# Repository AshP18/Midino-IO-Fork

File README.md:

# MIDIno IO

MIDIno is an open source project to make the best Midi controller. For now it works under the ATMEGA2560 processor architecture, in this case an Arduino Mega development board was used. In future versions it is expected to respond to other embedded architectures

## MIDIno functions

 - MIDIno has 16 programmable knobs (encoders), each one will have the possibility of being mapped in any DAW (Digital Audio Workstation). If you want to control an delay, some reverb or any parameter of a digital instrument you can do it. 

- Midino also works as a Beat Machine, add instruments and play them with your MIDIno, press the knobs and create music.

## Important READMEs
 - [Arduino OneButton Library](https://github.com/Rguarnizo/Midino-IO/blob/master/lib/OneButton/README.md)
   - Includes information regarding the usage/purpose of the OneButton library.
 - [Arduino MIDI Library](https://github.com/Rguarnizo/Midino-IO/blob/master/lib/MIDI_Library/README.md)
   - Includes information regarding the usage/purpose of the MIDI_Library library.
 - [Protothreads Library](https://github.com/Rguarnizo/Midino-IO/blob/master/lib/Protothreads/README.md)
   - Includes information regarding the usage/purpose of the Protothreads library.

If you want to contribute with the project, read the CONTRIBUTING.md file.

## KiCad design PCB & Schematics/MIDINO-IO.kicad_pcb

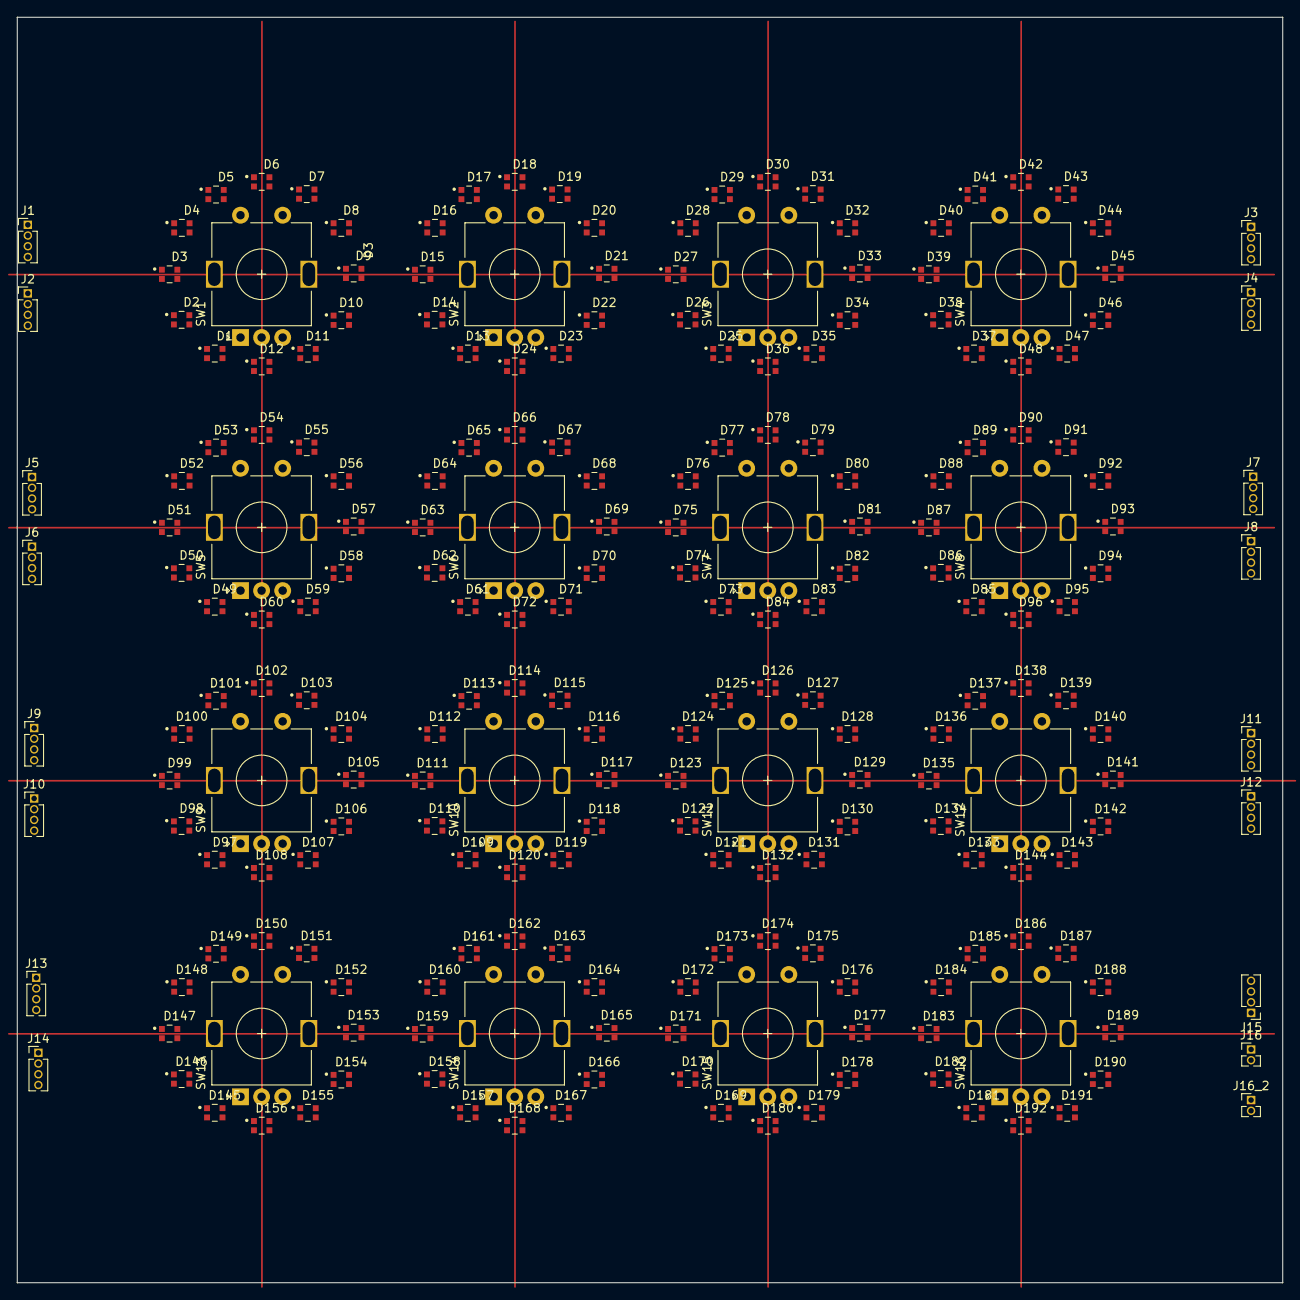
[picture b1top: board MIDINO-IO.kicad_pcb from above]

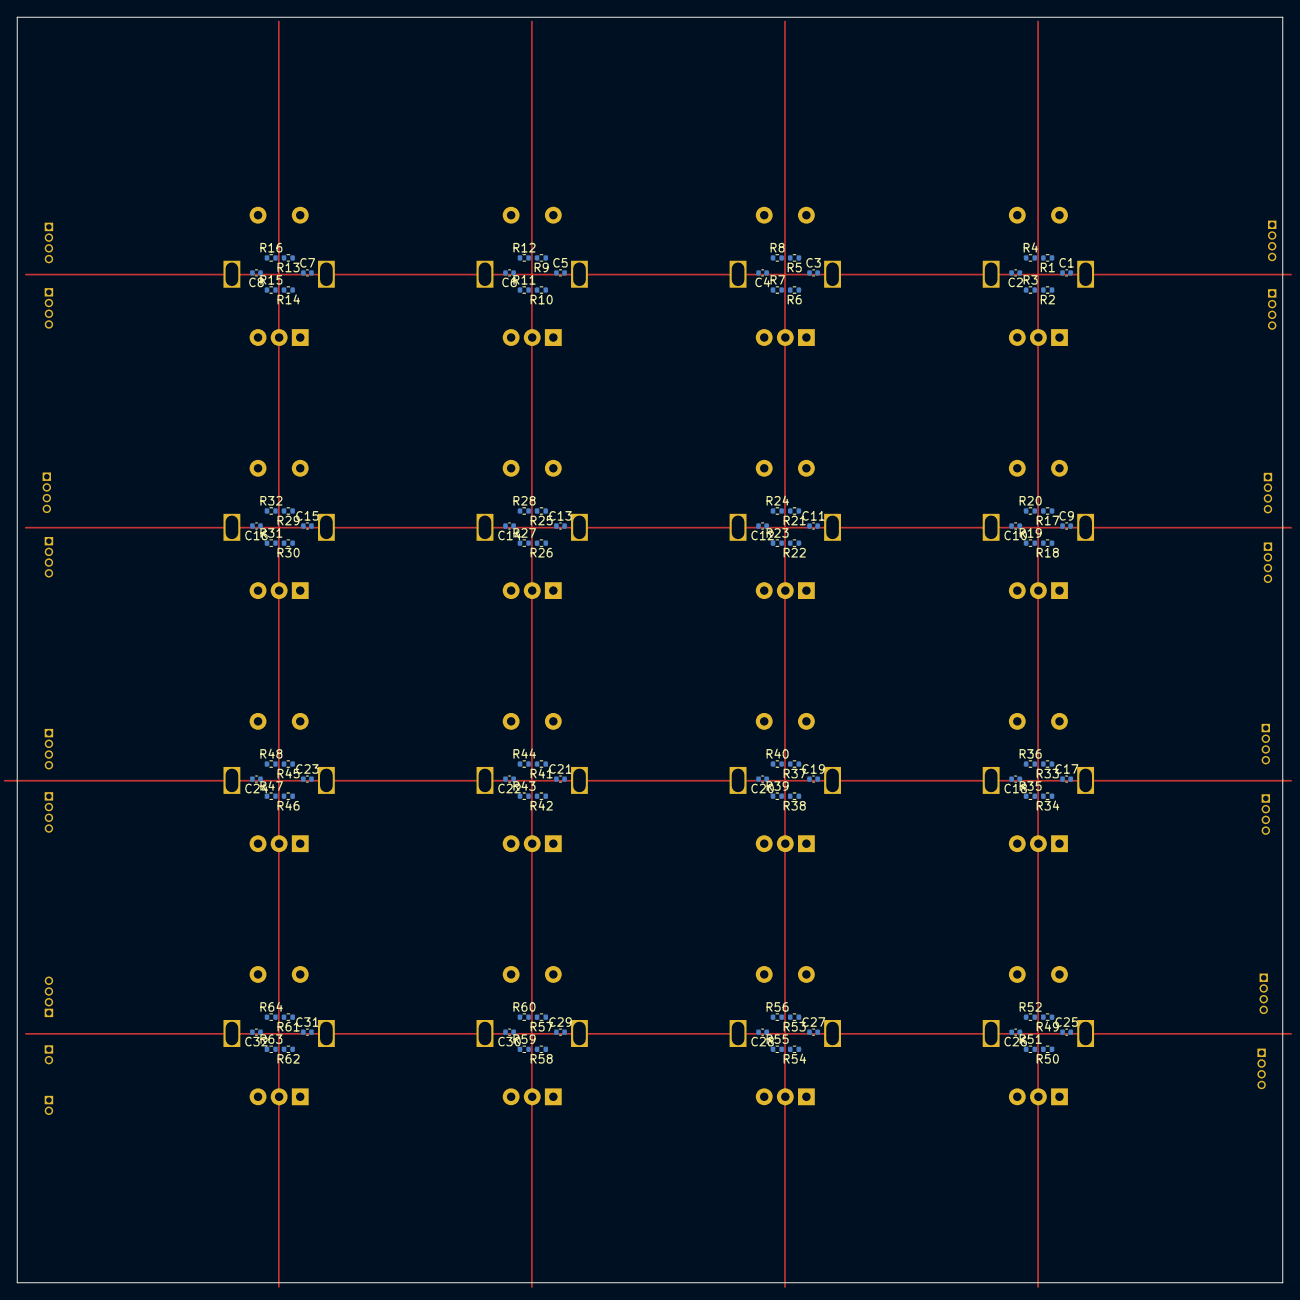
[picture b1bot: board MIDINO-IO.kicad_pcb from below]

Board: 2 copper layers, 150.0 x 150.0 mm, 321 parts (96 on the bottom side), 274 nets, no tracks yet.

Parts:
C1, C2, C3, C4, C5, C6, C7, C8, C9, C10, C11, C12, C13, C14, C15, C16, C17, C18, C19, C20, C21, C22, C23, C24, C25, C26, C27, C28, C29, C30, C31, C32: C; C_0402_1005Metric
D1, D2, D3, D4, D5, D6, D7, D8, D9, D10, D11, D12, D13, D14, D15, D16, D17, D18, D19, D20, D21, D22, D23, D24, D25, D26, D27, D28, D29, D30, D31, D32, D33, D34, D35, D36, D37, D38, D39, D40, D41, D42, D43, D44, D45, D46, D47, D48, D49, D50, D51, D52, D53, D54, D55, D56, D57, D58, D59, D60, D61, D62, D63, D64, D65, D66, D67, D68, D69, D70, D71, D72, D73, D74, D75, D76, D77, D78, D79, D80, D81, D82, D83, D84, D85, D86, D87, D88, D89, D90, D91, D92, D93, D94, D95, D96, D97, D98, D99, D100, D101, D102, D103, D104, D105, D106, D107, D108, D109, D110, D111, D112, D113, D114, D115, D116, D117, D118, D119, D120, D121, D122, D123, D124, D125, D126, D127, D128, D129, D130, D131, D132, D133, D134, D135, D136, D137, D138, D139, D140, D141, D142, D143, D144, D145, D146, D147, D148, D149, D150, D151, D152, D153, D154, D155, D156, D157, D158, D159, D160, D161, D162, D163, D164, D165, D166, D167, D168, D169, D170, D171, D172, D173, D174, D175, D176, D177, D178, D179, D180, D181, D182, D183, D184, D185, D186, D187, D188, D189, D190, D191, D192: WS2812B; LED_WS2812-2020
J1, J2, J3, J4, J5, J6, J7, J8, J9, J10, J11, J12, J13, J14, J15: Conn_01x04_Female; PinHeader_1x04_P1.27mm_Vertical
J16, J16_2: Conn_01x02_Female; PinHeader_1x02_P1.27mm_Vertical
R1, R2, R3, R4, R5, R6, R7, R8, R9, R10, R11, R12, R13, R14, R15, R16, R17, R18, R19, R20, R21, R22, R23, R24, R25, R26, R27, R28, R29, R30, R31, R32, R33, R34, R35, R36, R37, R38, R39, R40, R41, R42, R43, R44, R45, R46, R47, R48, R49, R50, R51, R52, R53, R54, R55, R56, R57, R58, R59, R60, R61, R62, R63, R64: 10K; R_0402_1005Metric
SW1, SW2, SW3, SW4, SW5, SW6, SW7, SW8, SW9, SW10, SW11, SW12, SW13, SW14, SW15, SW16: RotaryEncoder_Switch; RotaryEncoder_Alps_EC11E-Switch_Vertical_H20mm

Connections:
+5V: D1.1 (VDD), D2.1 (VDD), D3.1 (VDD), D4.1 (VDD), D5.1 (VDD), D6.1 (VDD), D7.1 (VDD), D8.1 (VDD), D9.1 (VDD), D10.1 (VDD), D11.1 (VDD), D12.1 (VDD), D13.1 (VDD), D14.1 (VDD), D15.1 (VDD), D16.1 (VDD), D17.1 (VDD), D18.1 (VDD), D19.1 (VDD), D20.1 (VDD), D21.1 (VDD), D22.1 (VDD), D23.1 (VDD), D24.1 (VDD), D25.1 (VDD), D26.1 (VDD), D27.1 (VDD), D28.1 (VDD), D29.1 (VDD), D30.1 (VDD), D31.1 (VDD), D32.1 (VDD), D33.1 (VDD), D34.1 (VDD), D35.1 (VDD), D36.1 (VDD), D37.1 (VDD), D38.1 (VDD), D39.1 (VDD), D40.1 (VDD), D41.1 (VDD), D42.1 (VDD), D43.1 (VDD), D44.1 (VDD), D45.1 (VDD), D46.1 (VDD), D47.1 (VDD), D48.1 (VDD), D49.1 (VDD), D50.1 (VDD), D51.1 (VDD), D52.1 (VDD), D53.1 (VDD), D54.1 (VDD), D55.1 (VDD), D56.1 (VDD), D57.1 (VDD), D58.1 (VDD), D59.1 (VDD), D60.1 (VDD), D61.1 (VDD), D62.1 (VDD), D63.1 (VDD), D64.1 (VDD), D65.1 (VDD), D66.1 (VDD), D67.1 (VDD), D68.1 (VDD), D69.1 (VDD), D70.1 (VDD), D71.1 (VDD), D72.1 (VDD), D73.1 (VDD), D74.1 (VDD), D75.1 (VDD), D76.1 (VDD), D77.1 (VDD), D78.1 (VDD), D79.1 (VDD), D80.1 (VDD), D81.1 (VDD), D82.1 (VDD), D83.1 (VDD), D84.1 (VDD), D85.1 (VDD), D86.1 (VDD), D87.1 (VDD), D88.1 (VDD), D89.1 (VDD), D90.1 (VDD), D91.1 (VDD), D92.1 (VDD), D93.1 (VDD), D94.1 (VDD), D95.1 (VDD), D96.1 (VDD), D97.1 (VDD), D98.1 (VDD), D99.1 (VDD), D100.1 (VDD), D101.1 (VDD), D102.1 (VDD), D103.1 (VDD), D104.1 (VDD), D105.1 (VDD), D106.1 (VDD), D107.1 (VDD), D108.1 (VDD), D109.1 (VDD), D110.1 (VDD), D111.1 (VDD), D112.1 (VDD), D113.1 (VDD), D114.1 (VDD), D115.1 (VDD), D116.1 (VDD), D117.1 (VDD), D118.1 (VDD), D119.1 (VDD), D120.1 (VDD), D121.1 (VDD), D122.1 (VDD), D123.1 (VDD), D124.1 (VDD), D125.1 (VDD), D126.1 (VDD), D127.1 (VDD), D128.1 (VDD), D129.1 (VDD), D130.1 (VDD), D131.1 (VDD), D132.1 (VDD), D133.1 (VDD), D134.1 (VDD), D135.1 (VDD), D136.1 (VDD), D137.1 (VDD), D138.1 (VDD), D139.1 (VDD), D140.1 (VDD), D141.1 (VDD), D142.1 (VDD), D143.1 (VDD), D144.1 (VDD), D145.1 (VDD), D146.1 (VDD), D147.1 (VDD), D148.1 (VDD), D149.1 (VDD), D150.1 (VDD), D151.1 (VDD), D152.1 (VDD), D153.1 (VDD), D154.1 (VDD), D155.1 (VDD), D156.1 (VDD), D157.1 (VDD), D158.1 (VDD), D159.1 (VDD), D160.1 (VDD), D161.1 (VDD), D162.1 (VDD), D163.1 (VDD), D164.1 (VDD), D165.1 (VDD), D166.1 (VDD), D167.1 (VDD), D168.1 (VDD), D169.1 (VDD), D170.1 (VDD), D171.1 (VDD), D172.1 (VDD), D173.1 (VDD), D174.1 (VDD), D175.1 (VDD), D176.1 (VDD), D177.1 (VDD), D178.1 (VDD), D179.1 (VDD), D180.1 (VDD), D181.1 (VDD), D182.1 (VDD), D183.1 (VDD), D184.1 (VDD), D185.1 (VDD), D186.1 (VDD), D187.1 (VDD), D188.1 (VDD), D189.1 (VDD), D190.1 (VDD), D191.1 (VDD), D192.1 (VDD), R2.2, R3.2, R6.2, R7.2, R10.2, R11.2, R14.2, R15.2, R18.2, R19.2, R22.2, R23.2, R26.2, R27.2, R30.2, R31.2, R34.2, R35.2, R38.2, R39.2, R42.2, R43.2, R46.2, R47.2, R50.2, R51.2, R54.2, R55.2, R58.2, R59.2, R62.2, R63.2
GND: C1.2, C2.2, C3.2, C4.2, C5.2, C6.2, C7.2, C8.2, C9.2, C10.2, C11.2, C12.2, C13.2, C14.2, C15.2, C16.2, C17.2, C18.2, C19.2, C20.2, C21.2, C22.2, C23.2, C24.2, C25.2, C26.2, C27.2, C28.2, C29.2, C30.2, C31.2, C32.2, D1.3 (VSS), D2.3 (VSS), D3.3 (VSS), D4.3 (VSS), D5.3 (VSS), D6.3 (VSS), D7.3 (VSS), D8.3 (VSS), D9.3 (VSS), D10.3 (VSS), D11.3 (VSS), D12.3 (VSS), D13.3 (VSS), D14.3 (VSS), D15.3 (VSS), D16.3 (VSS), D17.3 (VSS), D18.3 (VSS), D19.3 (VSS), D20.3 (VSS), D21.3 (VSS), D22.3 (VSS), D23.3 (VSS), D24.3 (VSS), D25.3 (VSS), D26.3 (VSS), D27.3 (VSS), D28.3 (VSS), D29.3 (VSS), D30.3 (VSS), D31.3 (VSS), D32.3 (VSS), D33.3 (VSS), D34.3 (VSS), D35.3 (VSS), D36.3 (VSS), D37.3 (VSS), D38.3 (VSS), D39.3 (VSS), D40.3 (VSS), D41.3 (VSS), D42.3 (VSS), D43.3 (VSS), D44.3 (VSS), D45.3 (VSS), D46.3 (VSS), D47.3 (VSS), D48.3 (VSS), D49.3 (VSS), D50.3 (VSS), D51.3 (VSS), D52.3 (VSS), D53.3 (VSS), D54.3 (VSS), D55.3 (VSS), D56.3 (VSS), D57.3 (VSS), D58.3 (VSS), D59.3 (VSS), D60.3 (VSS), D61.3 (VSS), D62.3 (VSS), D63.3 (VSS), D64.3 (VSS), D65.3 (VSS), D66.3 (VSS), D67.3 (VSS), D68.3 (VSS), D69.3 (VSS), D70.3 (VSS), D71.3 (VSS), D72.3 (VSS), D73.3 (VSS), D74.3 (VSS), D75.3 (VSS), D76.3 (VSS), D77.3 (VSS), D78.3 (VSS), D79.3 (VSS), D80.3 (VSS), D81.3 (VSS), D82.3 (VSS), D83.3 (VSS), D84.3 (VSS), D85.3 (VSS), D86.3 (VSS), D87.3 (VSS), D88.3 (VSS), D89.3 (VSS), D90.3 (VSS), D91.3 (VSS), D92.3 (VSS), D93.3 (VSS), D94.3 (VSS), D95.3 (VSS), D96.3 (VSS), D97.3 (VSS), D98.3 (VSS), D99.3 (VSS), D100.3 (VSS), D101.3 (VSS), D102.3 (VSS), D103.3 (VSS), D104.3 (VSS), D105.3 (VSS), D106.3 (VSS), D107.3 (VSS), D108.3 (VSS), D109.3 (VSS), D110.3 (VSS), D111.3 (VSS), D112.3 (VSS), D113.3 (VSS), D114.3 (VSS), D115.3 (VSS), D116.3 (VSS), D117.3 (VSS), D118.3 (VSS), D119.3 (VSS), D120.3 (VSS), D121.3 (VSS), D122.3 (VSS), D123.3 (VSS), D124.3 (VSS), D125.3 (VSS), D126.3 (VSS), D127.3 (VSS), D128.3 (VSS), D129.3 (VSS), D130.3 (VSS), D131.3 (VSS), D132.3 (VSS), D133.3 (VSS), D134.3 (VSS), D135.3 (VSS), D136.3 (VSS), D137.3 (VSS), D138.3 (VSS), D139.3 (VSS), D140.3 (VSS), D141.3 (VSS), D142.3 (VSS), D143.3 (VSS), D144.3 (VSS), D145.3 (VSS), D146.3 (VSS), D147.3 (VSS), D148.3 (VSS), D149.3 (VSS), D150.3 (VSS), D151.3 (VSS), D152.3 (VSS), D153.3 (VSS), D154.3 (VSS), D155.3 (VSS), D156.3 (VSS), D157.3 (VSS), D158.3 (VSS), D159.3 (VSS), D160.3 (VSS), D161.3 (VSS), D162.3 (VSS), D163.3 (VSS), D164.3 (VSS), D165.3 (VSS), D166.3 (VSS), D167.3 (VSS), D168.3 (VSS), D169.3 (VSS), D170.3 (VSS), D171.3 (VSS), D172.3 (VSS), D173.3 (VSS), D174.3 (VSS), D175.3 (VSS), D176.3 (VSS), D177.3 (VSS), D178.3 (VSS), D179.3 (VSS), D180.3 (VSS), D181.3 (VSS), D182.3 (VSS), D183.3 (VSS), D184.3 (VSS), D185.3 (VSS), D186.3 (VSS), D187.3 (VSS), D188.3 (VSS), D189.3 (VSS), D190.3 (VSS), D191.3 (VSS), D192.3 (VSS), SW1.C, SW1.S1, SW2.C, SW2.S1, SW3.C, SW3.S1, SW4.C, SW4.S1, SW5.C, SW5.S1, SW6.C, SW6.S1, SW7.C, SW7.S1, SW8.C, SW8.S1, SW9.C, SW9.S1, SW10.C, SW10.S1, SW11.C, SW11.S1, SW12.C, SW12.S1, SW13.C, SW13.S1, SW14.C, SW14.S1, SW15.C, SW15.S1, SW16.C, SW16.S1
unnamed: C1.1, R1.1, R2.1, SW1.A
unnamed: C2.1, R3.1, R4.1, SW1.B
unnamed: C3.1, R5.1, R6.1, SW2.A
unnamed: C4.1, R7.1, R8.1, SW2.B
unnamed: C5.1, R9.1, R10.1, SW3.A
unnamed: C6.1, R11.1, R12.1, SW3.B
unnamed: C7.1, R13.1, R14.1, SW4.A
unnamed: C8.1, R15.1, R16.1, SW4.B
unnamed: C9.1, R17.1, R18.1, SW5.A
unnamed: C10.1, R19.1, R20.1, SW5.B
unnamed: C11.1, R21.1, R22.1, SW6.A
unnamed: C12.1, R23.1, R24.1, SW6.B
unnamed: C13.1, R25.1, R26.1, SW7.A
unnamed: C14.1, R27.1, R28.1, SW7.B
unnamed: C15.1, R29.1, R30.1, SW8.A
unnamed: C16.1, R31.1, R32.1, SW8.B
unnamed: C17.1, R33.1, R34.1, SW9.A
unnamed: C18.1, R35.1, R36.1, SW9.B
unnamed: C19.1, R37.1, R38.1, SW10.A
unnamed: C20.1, R39.1, R40.1, SW10.B
unnamed: C21.1, R41.1, R42.1, SW11.A
unnamed: C22.1, R43.1, R44.1, SW11.B
unnamed: C23.1, R45.1, R46.1, SW12.A
unnamed: C24.1, R47.1, R48.1, SW12.B
unnamed: C25.1, R49.1, R50.1, SW13.A
unnamed: C26.1, R51.1, R52.1, SW13.B
unnamed: C27.1, R53.1, R54.1, SW14.A
unnamed: C28.1, R55.1, R56.1, SW14.B
unnamed: C29.1, R57.1, R58.1, SW15.A
unnamed: C30.1, R59.1, R60.1, SW15.B
unnamed: C31.1, R61.1, R62.1, SW16.A
unnamed: C32.1, R63.1, R64.1, SW16.B
unnamed: D1.4 (DIN), D2.2 (DOUT)
unnamed: D2.4 (DIN), D3.2 (DOUT)
unnamed: D3.4 (DIN), D4.2 (DOUT)
unnamed: D4.4 (DIN), D5.2 (DOUT)
unnamed: D5.4 (DIN), D6.2 (DOUT)
unnamed: D6.4 (DIN), D7.2 (DOUT)
unnamed: D7.4 (DIN), D8.2 (DOUT)
unnamed: D8.4 (DIN), D9.2 (DOUT)
unnamed: D9.4 (DIN), D10.2 (DOUT)
unnamed: D10.4 (DIN), D11.2 (DOUT)
unnamed: D11.4 (DIN), D12.2 (DOUT)
unnamed: D12.4 (DIN), J1.4
unnamed: D13.4 (DIN), D14.2 (DOUT)
unnamed: D14.4 (DIN), D15.2 (DOUT)
unnamed: D15.4 (DIN), D16.2 (DOUT)
unnamed: D16.4 (DIN), D17.2 (DOUT)
unnamed: D17.4 (DIN), D18.2 (DOUT)
unnamed: D18.4 (DIN), D19.2 (DOUT)
unnamed: D19.4 (DIN), D20.2 (DOUT)
unnamed: D20.4 (DIN), D21.2 (DOUT)
unnamed: D21.4 (DIN), D22.2 (DOUT)
unnamed: D22.4 (DIN), D23.2 (DOUT)
unnamed: D23.4 (DIN), D24.2 (DOUT)
unnamed: D24.4 (DIN), J2.4
unnamed: D25.4 (DIN), D26.2 (DOUT)
unnamed: D26.4 (DIN), D27.2 (DOUT)
unnamed: D27.4 (DIN), D28.2 (DOUT)
unnamed: D28.4 (DIN), D29.2 (DOUT)
unnamed: D29.4 (DIN), D30.2 (DOUT)
unnamed: D30.4 (DIN), D31.2 (DOUT)
unnamed: D31.4 (DIN), D32.2 (DOUT)
unnamed: D32.4 (DIN), D33.2 (DOUT)
unnamed: D33.4 (DIN), D34.2 (DOUT)
unnamed: D34.4 (DIN), D35.2 (DOUT)
unnamed: D35.4 (DIN), D36.2 (DOUT)
unnamed: D36.4 (DIN), J3.4
unnamed: D37.4 (DIN), D38.2 (DOUT)
unnamed: D38.4 (DIN), D39.2 (DOUT)
unnamed: D39.4 (DIN), D40.2 (DOUT)
unnamed: D40.4 (DIN), D41.2 (DOUT)
unnamed: D41.4 (DIN), D42.2 (DOUT)
unnamed: D42.4 (DIN), D43.2 (DOUT)
unnamed: D43.4 (DIN), D44.2 (DOUT)
unnamed: D44.4 (DIN), D45.2 (DOUT)
unnamed: D45.4 (DIN), D46.2 (DOUT)
unnamed: D46.4 (DIN), D47.2 (DOUT)
unnamed: D47.4 (DIN), D48.2 (DOUT)
unnamed: D48.4 (DIN), J4.4
unnamed: D49.4 (DIN), D50.2 (DOUT)
unnamed: D50.4 (DIN), D51.2 (DOUT)
unnamed: D51.4 (DIN), D52.2 (DOUT)
unnamed: D52.4 (DIN), D53.2 (DOUT)
unnamed: D53.4 (DIN), D54.2 (DOUT)
unnamed: D54.4 (DIN), D55.2 (DOUT)
unnamed: D55.4 (DIN), D56.2 (DOUT)
unnamed: D56.4 (DIN), D57.2 (DOUT)
unnamed: D57.4 (DIN), D58.2 (DOUT)
unnamed: D58.4 (DIN), D59.2 (DOUT)
unnamed: D59.4 (DIN), D60.2 (DOUT)
unnamed: D60.4 (DIN), J5.4
unnamed: D61.4 (DIN), D62.2 (DOUT)
unnamed: D62.4 (DIN), D63.2 (DOUT)
unnamed: D63.4 (DIN), D64.2 (DOUT)
unnamed: D64.4 (DIN), D65.2 (DOUT)
unnamed: D65.4 (DIN), D66.2 (DOUT)
unnamed: D66.4 (DIN), D67.2 (DOUT)
unnamed: D67.4 (DIN), D68.2 (DOUT)
unnamed: D68.4 (DIN), D69.2 (DOUT)
unnamed: D69.4 (DIN), D70.2 (DOUT)
unnamed: D70.4 (DIN), D71.2 (DOUT)
unnamed: D71.4 (DIN), D72.2 (DOUT)
unnamed: D72.4 (DIN), J6.4
unnamed: D73.4 (DIN), D74.2 (DOUT)
unnamed: D74.4 (DIN), D75.2 (DOUT)
unnamed: D75.4 (DIN), D76.2 (DOUT)
unnamed: D76.4 (DIN), D77.2 (DOUT)
unnamed: D77.4 (DIN), D78.2 (DOUT)
unnamed: D78.4 (DIN), D79.2 (DOUT)
unnamed: D79.4 (DIN), D80.2 (DOUT)
unnamed: D80.4 (DIN), D81.2 (DOUT)
unnamed: D81.4 (DIN), D82.2 (DOUT)
unnamed: D82.4 (DIN), D83.2 (DOUT)
unnamed: D83.4 (DIN), D84.2 (DOUT)
unnamed: D84.4 (DIN), J7.4
unnamed: D85.4 (DIN), D86.2 (DOUT)
unnamed: D86.4 (DIN), D87.2 (DOUT)
unnamed: D87.4 (DIN), D88.2 (DOUT)
unnamed: D88.4 (DIN), D89.2 (DOUT)
unnamed: D89.4 (DIN), D90.2 (DOUT)
unnamed: D90.4 (DIN), D91.2 (DOUT)
unnamed: D91.4 (DIN), D92.2 (DOUT)
unnamed: D92.4 (DIN), D93.2 (DOUT)
unnamed: D93.4 (DIN), D94.2 (DOUT)
unnamed: D94.4 (DIN), D95.2 (DOUT)
unnamed: D95.4 (DIN), D96.2 (DOUT)
unnamed: D96.4 (DIN), J8.4
unnamed: D97.4 (DIN), D98.2 (DOUT)
unnamed: D98.4 (DIN), D99.2 (DOUT)
unnamed: D99.4 (DIN), D100.2 (DOUT)
unnamed: D100.4 (DIN), D101.2 (DOUT)
unnamed: D101.4 (DIN), D102.2 (DOUT)
unnamed: D102.4 (DIN), D103.2 (DOUT)
unnamed: D103.4 (DIN), D104.2 (DOUT)
unnamed: D104.4 (DIN), D105.2 (DOUT)
unnamed: D105.4 (DIN), D106.2 (DOUT)
unnamed: D106.4 (DIN), D107.2 (DOUT)
unnamed: D107.4 (DIN), D108.2 (DOUT)
unnamed: D108.4 (DIN), J9.4
unnamed: D109.4 (DIN), D110.2 (DOUT)
unnamed: D110.4 (DIN), D111.2 (DOUT)
unnamed: D111.4 (DIN), D112.2 (DOUT)
unnamed: D112.4 (DIN), D113.2 (DOUT)
unnamed: D113.4 (DIN), D114.2 (DOUT)
unnamed: D114.4 (DIN), D115.2 (DOUT)
unnamed: D115.4 (DIN), D116.2 (DOUT)
unnamed: D116.4 (DIN), D117.2 (DOUT)
unnamed: D117.4 (DIN), D118.2 (DOUT)
unnamed: D118.4 (DIN), D119.2 (DOUT)
unnamed: D119.4 (DIN), D120.2 (DOUT)
unnamed: D120.4 (DIN), J10.4
unnamed: D121.4 (DIN), D122.2 (DOUT)
unnamed: D122.4 (DIN), D123.2 (DOUT)
unnamed: D123.4 (DIN), D124.2 (DOUT)
unnamed: D124.4 (DIN), D125.2 (DOUT)
unnamed: D125.4 (DIN), D126.2 (DOUT)
unnamed: D126.4 (DIN), D127.2 (DOUT)
unnamed: D127.4 (DIN), D128.2 (DOUT)
unnamed: D128.4 (DIN), D129.2 (DOUT)
unnamed: D129.4 (DIN), D130.2 (DOUT)
unnamed: D130.4 (DIN), D131.2 (DOUT)
unnamed: D131.4 (DIN), D132.2 (DOUT)
unnamed: D132.4 (DIN), J11.4
unnamed: D133.4 (DIN), D134.2 (DOUT)
unnamed: D134.4 (DIN), D135.2 (DOUT)
unnamed: D135.4 (DIN), D136.2 (DOUT)
unnamed: D136.4 (DIN), D137.2 (DOUT)
unnamed: D137.4 (DIN), D138.2 (DOUT)
unnamed: D138.4 (DIN), D139.2 (DOUT)
unnamed: D139.4 (DIN), D140.2 (DOUT)
unnamed: D140.4 (DIN), D141.2 (DOUT)
unnamed: D141.4 (DIN), D142.2 (DOUT)
unnamed: D142.4 (DIN), D143.2 (DOUT)
unnamed: D143.4 (DIN), D144.2 (DOUT)
unnamed: D145.4 (DIN), D146.2 (DOUT)
unnamed: D146.4 (DIN), D147.2 (DOUT)
unnamed: D147.4 (DIN), D148.2 (DOUT)
unnamed: D148.4 (DIN), D149.2 (DOUT)
unnamed: D149.4 (DIN), D150.2 (DOUT)
unnamed: D150.4 (DIN), D151.2 (DOUT)
unnamed: D151.4 (DIN), D152.2 (DOUT)
unnamed: D152.4 (DIN), D153.2 (DOUT)
unnamed: D153.4 (DIN), D154.2 (DOUT)
unnamed: D154.4 (DIN), D155.2 (DOUT)
unnamed: D155.4 (DIN), D156.2 (DOUT)
unnamed: D156.4 (DIN), J13.1
unnamed: D157.4 (DIN), D158.2 (DOUT)
unnamed: D158.4 (DIN), D159.2 (DOUT)
unnamed: D159.4 (DIN), D160.2 (DOUT)
unnamed: D160.4 (DIN), D161.2 (DOUT)
unnamed: D161.4 (DIN), D162.2 (DOUT)
unnamed: D162.4 (DIN), D163.2 (DOUT)
unnamed: D163.4 (DIN), D164.2 (DOUT)
unnamed: D164.4 (DIN), D165.2 (DOUT)
unnamed: D165.4 (DIN), D166.2 (DOUT)
unnamed: D166.4 (DIN), D167.2 (DOUT)
unnamed: D167.4 (DIN), D168.2 (DOUT)
unnamed: D169.4 (DIN), D170.2 (DOUT)
unnamed: D170.4 (DIN), D171.2 (DOUT)
unnamed: D171.4 (DIN), D172.2 (DOUT)
unnamed: D172.4 (DIN), D173.2 (DOUT)
unnamed: D173.4 (DIN), D174.2 (DOUT)
unnamed: D174.4 (DIN), D175.2 (DOUT)
unnamed: D175.4 (DIN), D176.2 (DOUT)
unnamed: D176.4 (DIN), D177.2 (DOUT)
unnamed: D177.4 (DIN), D178.2 (DOUT)
unnamed: D178.4 (DIN), D179.2 (DOUT)
unnamed: D179.4 (DIN), D180.2 (DOUT)
unnamed: D181.4 (DIN), D182.2 (DOUT)
unnamed: D182.4 (DIN), D183.2 (DOUT)
unnamed: D183.4 (DIN), D184.2 (DOUT)
unnamed: D184.4 (DIN), D185.2 (DOUT)
unnamed: D185.4 (DIN), D186.2 (DOUT)
unnamed: D186.4 (DIN), D187.2 (DOUT)
unnamed: D187.4 (DIN), D188.2 (DOUT)
unnamed: D188.4 (DIN), D189.2 (DOUT)
unnamed: D189.4 (DIN), D190.2 (DOUT)
unnamed: D190.4 (DIN), D191.2 (DOUT)
unnamed: D191.4 (DIN), D192.2 (DOUT)
unnamed: J1.1, R1.2
unnamed: J1.2, R4.2
unnamed: J1.3, SW1.S2
unnamed: J2.1, R5.2
unnamed: J2.2, R8.2
unnamed: J2.3, SW2.S2
unnamed: J3.1, R9.2
unnamed: J3.2, R12.2
unnamed: J3.3, SW3.S2
unnamed: J15.1, R61.2
unnamed: J15.2, R64.2
unnamed: J15.3, SW16.S2
unnamed: D192.4 (DIN), J15.4
unnamed: J16.1, R57.2
unnamed: J16.2, R60.2
unnamed: D180.4 (DIN), J16_2.1
unnamed: J16_2.2, SW15.S2
unnamed: J4.1, R13.2
unnamed: J4.2, R16.2
unnamed: J4.3, SW4.S2
unnamed: J5.1, R17.2
unnamed: J5.2, R20.2
unnamed: J5.3, SW5.S2
unnamed: J6.1, R21.2
unnamed: J6.2, R24.2
unnamed: J6.3, SW6.S2
unnamed: J7.1, R25.2
unnamed: J7.2, R28.2
unnamed: J7.3, SW7.S2
unnamed: J8.1, R29.2
unnamed: J8.2, R32.2
unnamed: J8.3, SW8.S2
unnamed: J9.1, R33.2
unnamed: J9.2, R36.2
unnamed: J9.3, SW9.S2
unnamed: J10.1, R37.2
unnamed: J10.2, R40.2
unnamed: J10.3, SW10.S2
unnamed: J11.1, R41.2
unnamed: J11.2, R44.2
unnamed: J11.3, SW11.S2
unnamed: D144.4 (DIN), J12.1
unnamed: J12.2, SW12.S2
unnamed: J12.3, R48.2
unnamed: J12.4, R45.2
unnamed: J13.2, SW13.S2
unnamed: J13.3, R52.2
unnamed: J13.4, R49.2
unnamed: D168.4 (DIN), J14.1
unnamed: J14.2, SW14.S2
unnamed: J14.3, R56.2
unnamed: J14.4, R53.2

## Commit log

2020-08-26 Upload all necesary paths and files.
    All the necessary files are uploaded to be able to start the project.
2020-08-26 README.md updated from https://stackedit.io/
2020-08-29 Add Libraries and part of the project
    Adding libraries and a piece of part of the project (send MIDI Message to buttons of knobs)
2020-10-04 Own implementation Knobs
    Knobs operation was implemented due to the library not working quite well.
2020-10-04 Delate no necessary libraries
    The encoder library was removed, since it is no longer needed
2020-10-04 Add Contributing.md and modify readme
    Add Contributing.md and modify readme
2020-10-19 Quitar librerias innecesarias.
2020-11-19 Update README.md
    Error typos in readme.
2022-03-05 Add PCB Schematics path
2022-08-03 Code modify to hiduino and schematics
2022-08-03 Add Routing to schematics
2024-02-14 Direct to librarys' READMEs
    Added a section to the main README that links to the librarys' READMEs to direct potential contributors to relevant information concerning what the added libraries provide and how they can be utilize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
